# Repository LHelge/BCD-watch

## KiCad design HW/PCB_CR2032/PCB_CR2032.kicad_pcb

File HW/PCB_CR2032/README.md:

# PCB_CR2032
Design of watch PCB to be used with a CR2032 coin cell battery

## Schematic
TODO: add this as images here

## BoM

Reference | Value | Make | Mouser part# | Part | Qty
--------- | ----- | ---- | ---- | ------ | ---
BT1 | CR2032 | Linx | 712-BAT-HLD-001 | BAT-HLD-001 | 1
C1, C2 | 20pF | Yageo | 603-CC805JRNPO9BN200 | CC0805JRNPO9BN200 | 2
C4-C9, C14, C15 | 100nF | Yageo | 603-CC805KRX7R9BB104 | CC0805KRX7R9BB104 | 8
C12 | 11mF | SII | 628-CPH3225A-2K | CPH3225A | 1
C3, C11, C13 | 10uF | Yageo | 603-CC805KKX7R6BB106 | CC0805KKX7R6BB106 | 3
D1-D3 | BAR43CFILM | ST | 511-BAR43CFILM | BAR43CFILM | 3
H00-H03,<br> H10-H13,<br> M00-M03,<br> M10-M13,<br> S00-S03,<br> S10-S13 | LED | Kingbright | 604-APTR3216SECKJ3 | APTR3216SECK/J3-PRV | 24
J1 | STDC14 | Amphenol  | 649-221121-00014T4LF | 20021121-00014T4LF | 1
R1-R20, R23-R26 | 1k | Yageo | 603-RC0805FR-071KL | RC0805FR-071KL | 24
R27-R31 | 10k | Yageo | 603-RC0805FR-0710KL | RC0805FR-0710KL | 5
SW1 | WAKE | Wurth | 710-434331045822 | 434331045822 | 1
U1 | STM32L071CBTx | ST | 511-STM32L071CBT6TR | STM32L071CBT6 | 1
U3 | LIS2DW12 | ST | 511-LIS2DW12TR | LIS2DW12TR | 1
Y1 | 32768 Hz | Epson Timing | 732-FC135-32.76KAA3 | FC-135 32.7680KA-A3 | 1

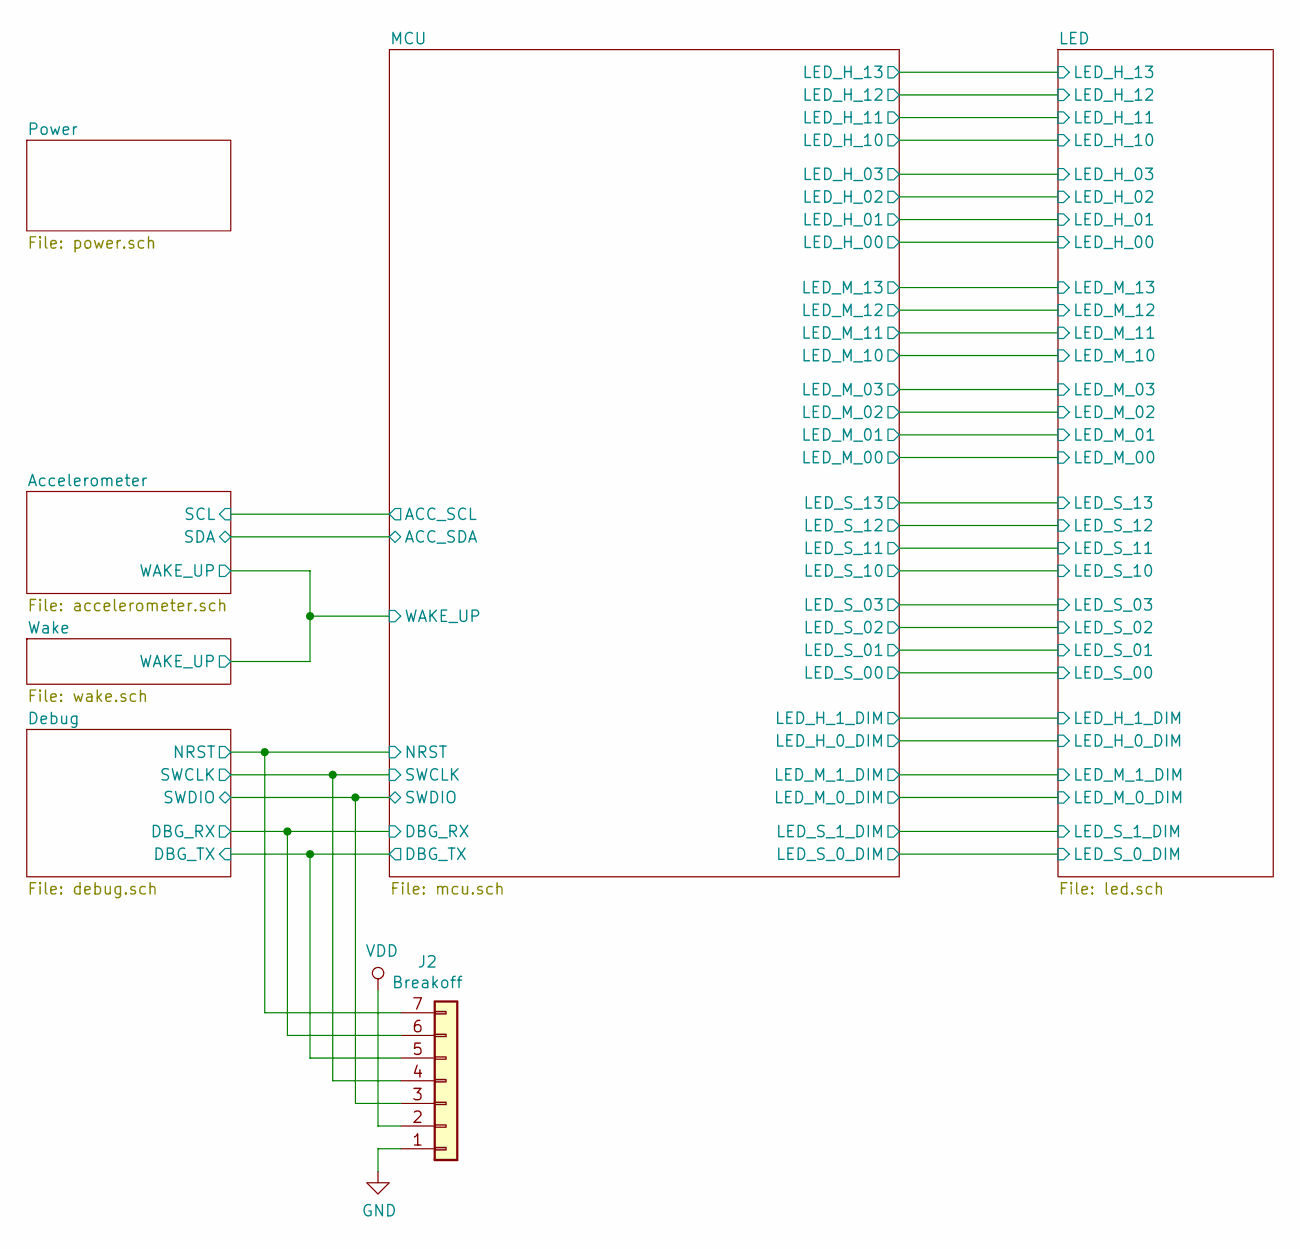
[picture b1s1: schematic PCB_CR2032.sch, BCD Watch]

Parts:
J2: Breakoff; PinHeader_1x07_P1.27mm_Vertical

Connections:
/Debug/DBG_RX: J2.6; also elsewhere on the board
/Debug/DBG_TX: J2.5; also elsewhere on the board
/Debug/NRST: J2.7; also elsewhere on the board
/Debug/SWCLK: J2.4; also elsewhere on the board
/Debug/SWDIO: J2.3; also elsewhere on the board
GND: J2.1; also elsewhere on the board
VDD: J2.2; also elsewhere on the board

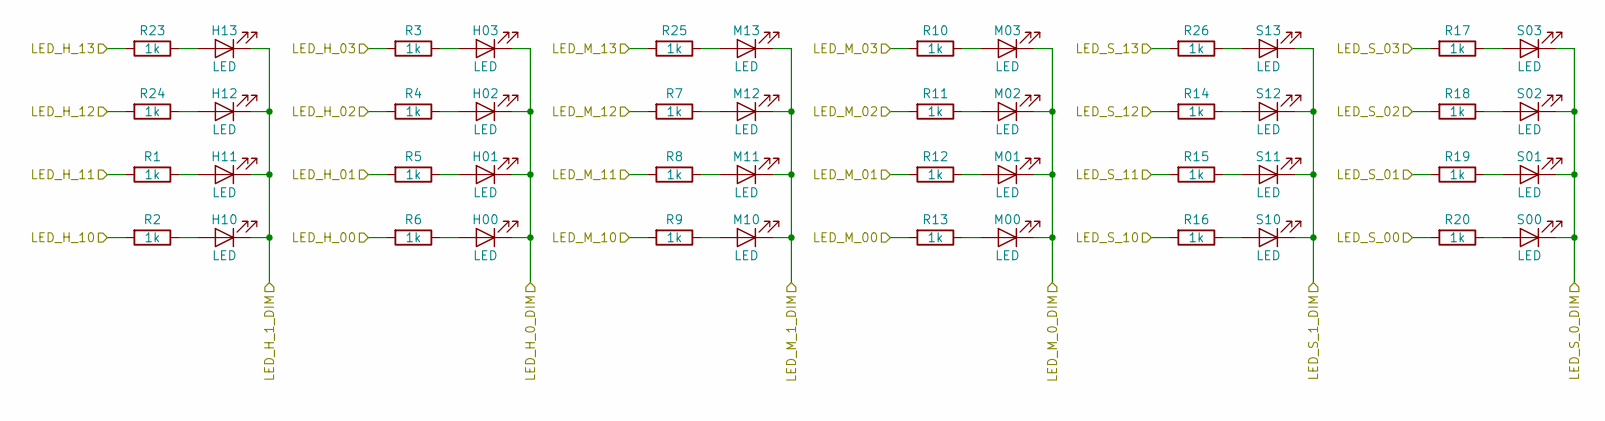
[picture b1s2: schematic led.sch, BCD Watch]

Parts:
H00, H01, H02, H03, H10, H11, H12, H13: LED; LED_1206_3216Metric; Part APTR3216SECK/J3-PRV; Mouser 604-APTR3216SECKJ3
M00, M01, M02, M03, M10, M11, M12, M13: LED; LED_1206_3216Metric; Part APTR3216SECK/J3-PRV; Mouser 604-APTR3216SECKJ3
R1, R2, R3, R4, R5, R6, R7, R8, R9, R10, R11, R12, R13, R14, R15, R16, R17, R18, R19, R20, R23, R24, R25, R26: 1k; R_0603_1608Metric_Pad1.05x0.95mm_HandSolder
S00, S01, S02, S03, S10, S11, S12, S13: LED; LED_1206_3216Metric; Part APTR3216SECK/J3-PRV; Mouser 604-APTR3216SECKJ3

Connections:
/Debug/DBG_RX: R23.2; also elsewhere on the board
/Debug/DBG_TX: R24.2; also elsewhere on the board
/LED/LED_H_00: R6.2; also elsewhere on the board
/LED/LED_H_0_DIM: H00.1 (K), H01.1 (K), H02.1 (K), H03.1 (K); also elsewhere on the board
/LED/LED_H_01: R5.2; also elsewhere on the board
/LED/LED_H_1_DIM: H10.1 (K), H11.1 (K), H12.1 (K), H13.1 (K); also elsewhere on the board
/LED/LED_H_02: R4.2; also elsewhere on the board
/LED/LED_H_03: R3.2; also elsewhere on the board
/LED/LED_H_10: R2.2; also elsewhere on the board
/LED/LED_H_11: R1.2; also elsewhere on the board
/LED/LED_M_00: R13.2; also elsewhere on the board
/LED/LED_M_0_DIM: M00.1 (K), M01.1 (K), M02.1 (K), M03.1 (K); also elsewhere on the board
/LED/LED_M_01: R12.2; also elsewhere on the board
/LED/LED_M_1_DIM: M10.1 (K), M11.1 (K), M12.1 (K), M13.1 (K); also elsewhere on the board
/LED/LED_M_02: R11.2; also elsewhere on the board
/LED/LED_M_03: R10.2; also elsewhere on the board
/LED/LED_M_10: R9.2; also elsewhere on the board
/LED/LED_M_11: R8.2; also elsewhere on the board
/LED/LED_M_12: R7.2; also elsewhere on the board
/LED/LED_M_13: R25.2; also elsewhere on the board
/LED/LED_S_00: R20.2; also elsewhere on the board
/LED/LED_S_0_DIM: S00.1 (K), S01.1 (K), S02.1 (K), S03.1 (K); also elsewhere on the board
/LED/LED_S_01: R19.2; also elsewhere on the board
/LED/LED_S_1_DIM: S10.1 (K), S11.1 (K), S12.1 (K), S13.1 (K); also elsewhere on the board
/LED/LED_S_02: R18.2; also elsewhere on the board
/LED/LED_S_03: R17.2; also elsewhere on the board
/LED/LED_S_10: R16.2; also elsewhere on the board
/LED/LED_S_11: R15.2; also elsewhere on the board
/LED/LED_S_12: R14.2; also elsewhere on the board
/LED/LED_S_13: R26.2; also elsewhere on the board
unnamed: H00.2 (A), R6.1
unnamed: H01.2 (A), R5.1
unnamed: H02.2 (A), R4.1
unnamed: H03.2 (A), R3.1
unnamed: H10.2 (A), R2.1
unnamed: H11.2 (A), R1.1
unnamed: H12.2 (A), R24.1
unnamed: H13.2 (A), R23.1
unnamed: M00.2 (A), R13.1
unnamed: M01.2 (A), R12.1
unnamed: M02.2 (A), R11.1
unnamed: M03.2 (A), R10.1
unnamed: M10.2 (A), R9.1
unnamed: M11.2 (A), R8.1
unnamed: M12.2 (A), R7.1
unnamed: M13.2 (A), R25.1
unnamed: R14.1, S12.2 (A)
unnamed: R15.1, S11.2 (A)
unnamed: R16.1, S10.2 (A)
unnamed: R17.1, S03.2 (A)
unnamed: R18.1, S02.2 (A)
unnamed: R19.1, S01.2 (A)
unnamed: R20.1, S00.2 (A)
unnamed: R26.1, S13.2 (A)

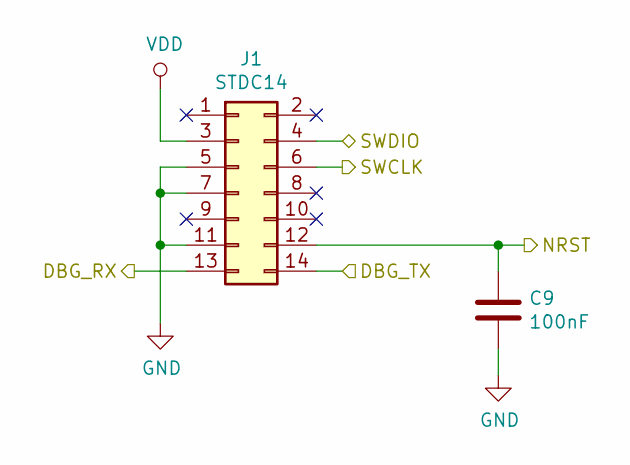
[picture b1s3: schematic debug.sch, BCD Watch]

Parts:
C9: 100nF; C_0603_1608Metric_Pad1.05x0.95mm_HandSolder; jlcpcb CC0603KRX7R9BB104
J1: STDC14; PinHeader_2x07_P1.27mm_Vertical_SMD; Part 20021121-00014T4LF; Mouser 649-221121-00014T4LF

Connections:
/Debug/DBG_RX: J1.13; also elsewhere on the board
/Debug/DBG_TX: J1.14; also elsewhere on the board
/Debug/NRST: C9.1, J1.12; also elsewhere on the board
/Debug/SWCLK: J1.6; also elsewhere on the board
/Debug/SWDIO: J1.4; also elsewhere on the board
GND: C9.2, J1.5, J1.7, J1.11; also elsewhere on the board
VDD: J1.3; also elsewhere on the board

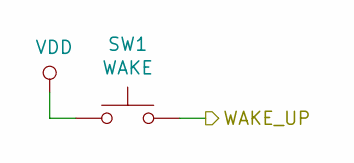
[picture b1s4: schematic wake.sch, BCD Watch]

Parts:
SW1: WAKE; WS-TASU SMT Tact Switch; Part 434331045822; Mouser 710-434331045822

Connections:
/Accelerometer/WAKE_UP: SW1.2; also elsewhere on the board
VDD: SW1.1; also elsewhere on the board

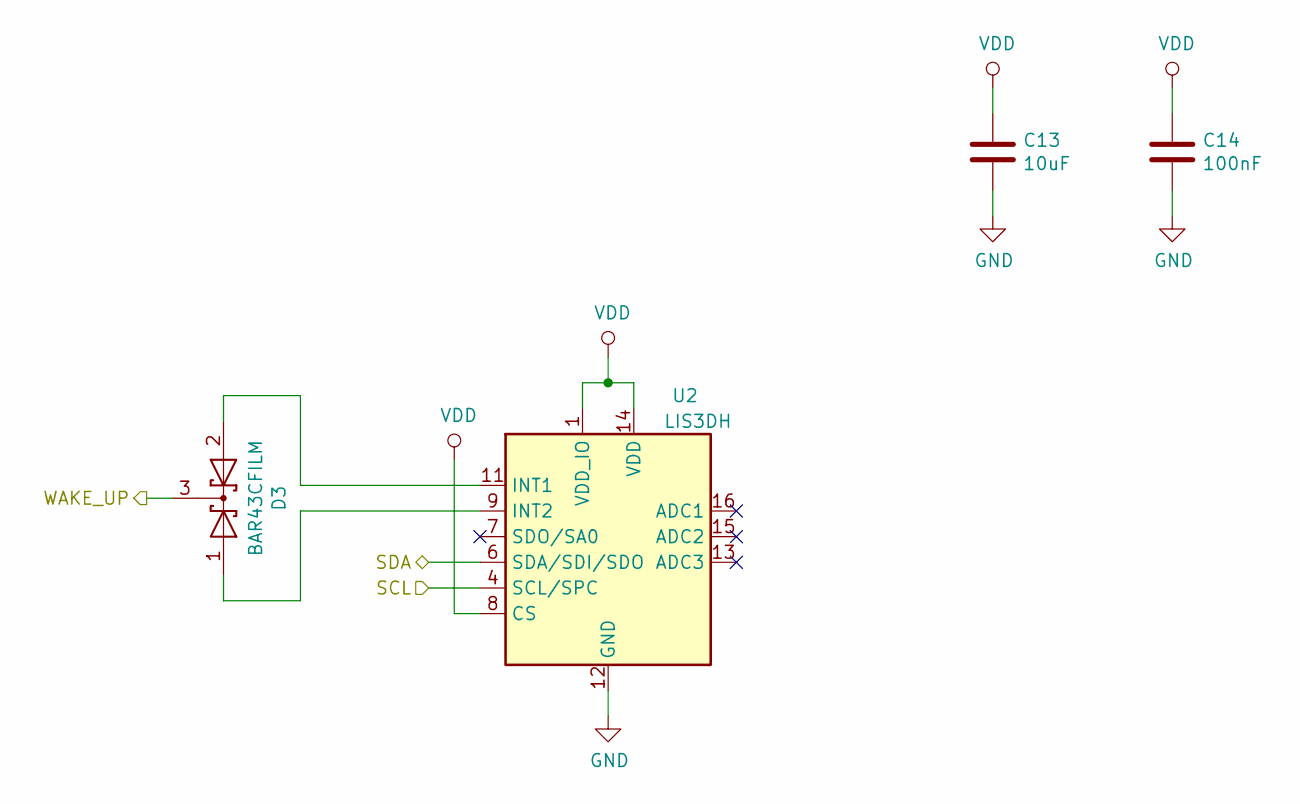
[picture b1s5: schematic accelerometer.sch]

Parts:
C13: 10uF; C_0805_2012Metric_Pad1.15x1.40mm_HandSolder; jlcpcb CL21A106KAYNNNE
C14: 100nF; C_0603_1608Metric_Pad1.05x0.95mm_HandSolder; jlcpcb CC0603KRX7R9BB104
D3: BAR43CFILM; SOT-23_Handsoldering; Part BAR43CFILM; Mouser 511-BAR43CFILM
U2: LIS3DH; LGA-16_3x3mm_P0.5mm_LayoutBorder3x5y; jlcpcb LIS3DHTR

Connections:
/Accelerometer/WAKE_UP: D3.3 (K); also elsewhere on the board
/MCU/ACC_SCL: U2.4 (SCL/SPC); also elsewhere on the board
/MCU/ACC_SDA: U2.6 (SDA/SDI/SDO); also elsewhere on the board
GND: C13.2, C14.2, U2.5 (GND), U2.10 (GND), U2.12 (GND); also elsewhere on the board
unnamed: D3.1 (A), U2.9 (INT2)
unnamed: D3.2 (A), U2.11 (INT1)
VDD: C13.1, C14.1, U2.1 (VDD_IO), U2.8 (CS), U2.14 (VDD); also elsewhere on the board

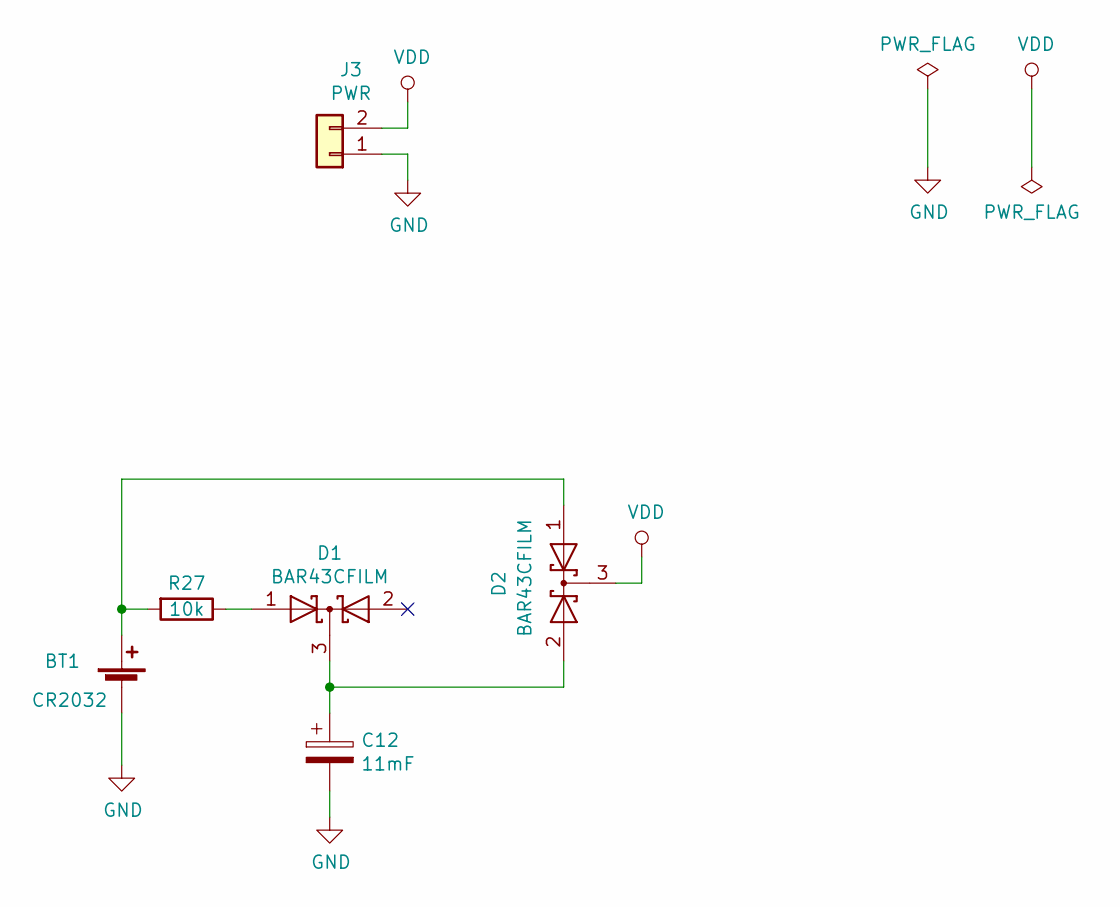
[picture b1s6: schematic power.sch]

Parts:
BT1: CR2032; BAT-HLD-001-xx-OTL; Part BAT-HLD-001; Mouser 712-BAT-HLD-001
C12: 11mF; CPH3225A; Part CPH3225A; Mouser 628-CPH3225A-2K
D1, D2: BAR43CFILM; SOT-23_Handsoldering; Part BAR43CFILM; Mouser 511-BAR43CFILM
J3: PWR; PinHeader_1x02_P1.27mm_Vertical
R27: 10k; R_0603_1608Metric_Pad1.05x0.95mm_HandSolder; LCSC C25804

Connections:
GND: BT1.2 (-), C12.2, J3.1; also elsewhere on the board
unnamed: BT1.1 (+), D2.1 (A), R27.2
unnamed: C12.1, D1.3 (K), D2.2 (A)
unnamed: D1.1 (A), R27.1
VDD: D2.3 (K), J3.2; also elsewhere on the board

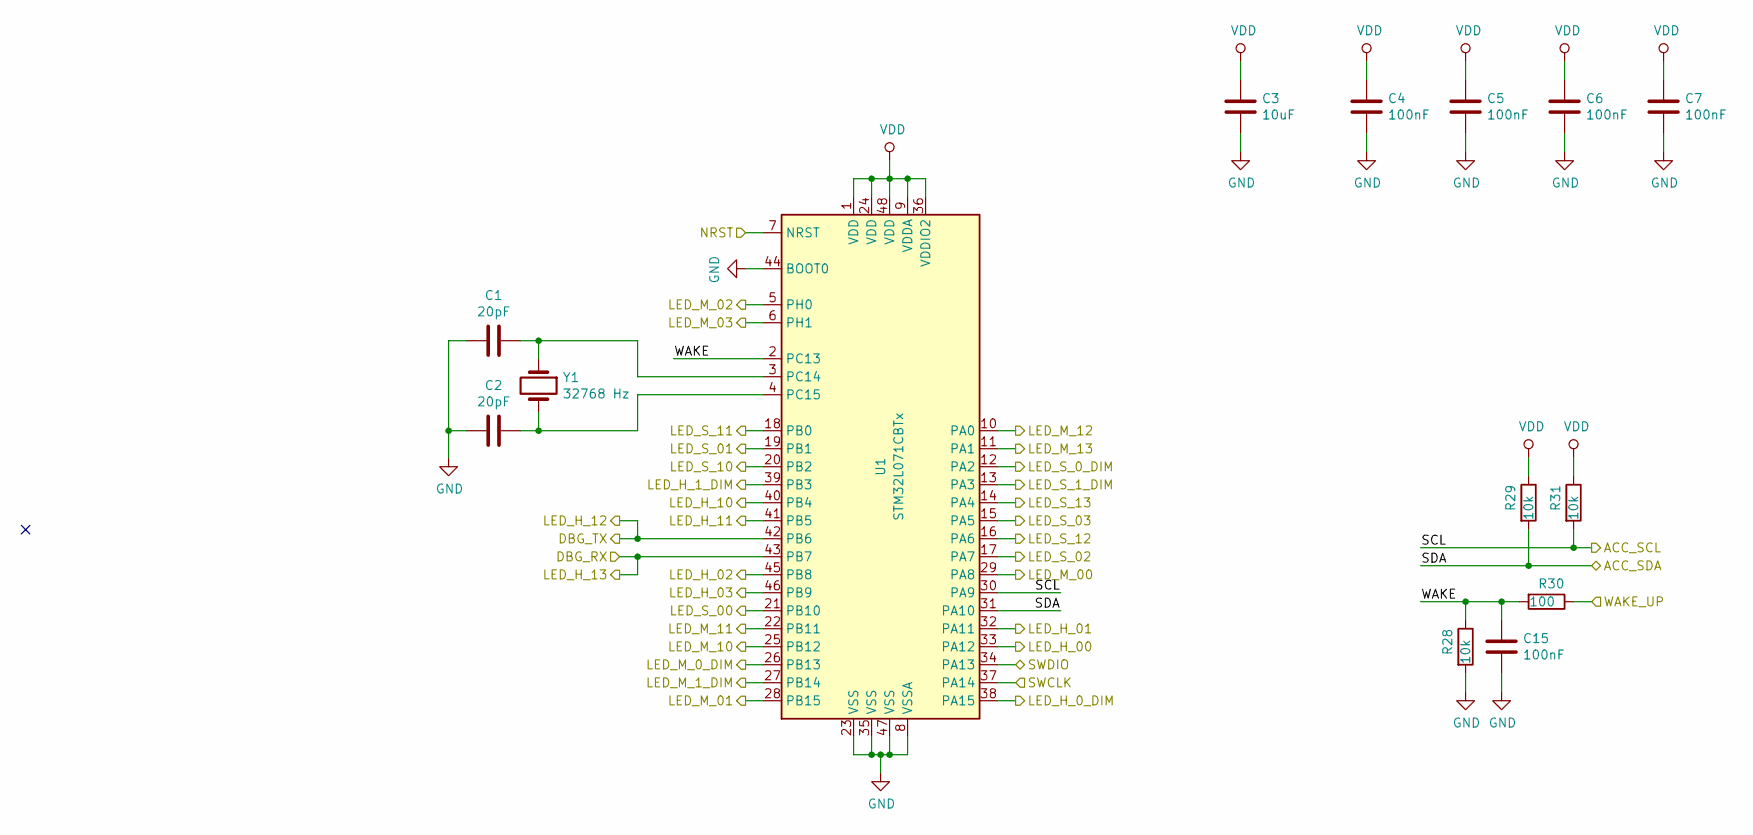
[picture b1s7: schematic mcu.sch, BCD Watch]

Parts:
C1, C2: 20pF; C_0603_1608Metric_Pad1.05x0.95mm_HandSolder; jlcpcb CL10C200JB8NNNC
C3: 10uF; C_0805_2012Metric_Pad1.15x1.40mm_HandSolder; jlcpcb CL21A106KAYNNNE
C4, C5, C6, C7, C15: 100nF; C_0603_1608Metric_Pad1.05x0.95mm_HandSolder; jlcpcb CC0603KRX7R9BB104
R28, R29, R31: 10k; R_0603_1608Metric_Pad1.05x0.95mm_HandSolder; LCSC C25804
R30: 100; R_0603_1608Metric_Pad1.05x0.95mm_HandSolder; LCSC C22775
U1: STM32L071CBTx; LQFP-48_7x7mm_P0.5mm; Part STM32L071CBT6; Mouser 511-STM32L071CBT6TR
Y1: 32768 Hz; FC-135; Part FC-135 32.7680KA-A3; Mouser 732-FC135-32.76KAA3

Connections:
/Accelerometer/WAKE_UP: R30.1; also elsewhere on the board
/Debug/DBG_RX: U1.43 (PB7); also elsewhere on the board
/Debug/DBG_TX: U1.42 (PB6); also elsewhere on the board
/Debug/NRST: U1.7 (NRST); also elsewhere on the board
/Debug/SWCLK: U1.37 (PA14); also elsewhere on the board
/Debug/SWDIO: U1.34 (PA13); also elsewhere on the board
/LED/LED_H_00: U1.33 (PA12); also elsewhere on the board
/LED/LED_H_0_DIM: U1.38 (PA15); also elsewhere on the board
/LED/LED_H_01: U1.32 (PA11); also elsewhere on the board
/LED/LED_H_1_DIM: U1.39 (PB3); also elsewhere on the board
/LED/LED_H_02: U1.45 (PB8); also elsewhere on the board
/LED/LED_H_03: U1.46 (PB9); also elsewhere on the board
/LED/LED_H_10: U1.40 (PB4); also elsewhere on the board
/LED/LED_H_11: U1.41 (PB5); also elsewhere on the board
/LED/LED_M_00: U1.29 (PA8); also elsewhere on the board
/LED/LED_M_0_DIM: U1.26 (PB13); also elsewhere on the board
/LED/LED_M_01: U1.28 (PB15); also elsewhere on the board
/LED/LED_M_1_DIM: U1.27 (PB14); also elsewhere on the board
/LED/LED_M_02: U1.5 (PH0); also elsewhere on the board
/LED/LED_M_03: U1.6 (PH1); also elsewhere on the board
/LED/LED_M_10: U1.25 (PB12); also elsewhere on the board
/LED/LED_M_11: U1.22 (PB11); also elsewhere on the board
/LED/LED_M_12: U1.10 (PA0); also elsewhere on the board
/LED/LED_M_13: U1.11 (PA1); also elsewhere on the board
/LED/LED_S_00: U1.21 (PB10); also elsewhere on the board
/LED/LED_S_0_DIM: U1.12 (PA2); also elsewhere on the board
/LED/LED_S_01: U1.19 (PB1); also elsewhere on the board
/LED/LED_S_1_DIM: U1.13 (PA3); also elsewhere on the board
/LED/LED_S_02: U1.17 (PA7); also elsewhere on the board
/LED/LED_S_03: U1.15 (PA5); also elsewhere on the board
/LED/LED_S_10: U1.20 (PB2); also elsewhere on the board
/LED/LED_S_11: U1.18 (PB0); also elsewhere on the board
/LED/LED_S_12: U1.16 (PA6); also elsewhere on the board
/LED/LED_S_13: U1.14 (PA4); also elsewhere on the board
/MCU/ACC_SCL: R31.2, U1.30 (PA9); also elsewhere on the board
/MCU/ACC_SDA: R29.2, U1.31 (PA10); also elsewhere on the board
/MCU/WAKE: C15.1, R28.1, R30.2, U1.2 (PC13)
GND: C1.2, C2.2, C3.2, C4.2, C5.2, C6.2, C7.2, C15.2, R28.2, U1.8 (VSSA), U1.23 (VSS), U1.35 (VSS), U1.44 (BOOT0), U1.47 (VSS); also elsewhere on the board
unnamed: C1.1, U1.3 (PC14), Y1.1
unnamed: C2.1, U1.4 (PC15), Y1.2
VDD: C3.1, C4.1, C5.1, C6.1, C7.1, R29.1, R31.1, U1.1 (VDD), U1.9 (VDDA), U1.24 (VDD), U1.36 (VDDIO2), U1.48 (VDD); also elsewhere on the board

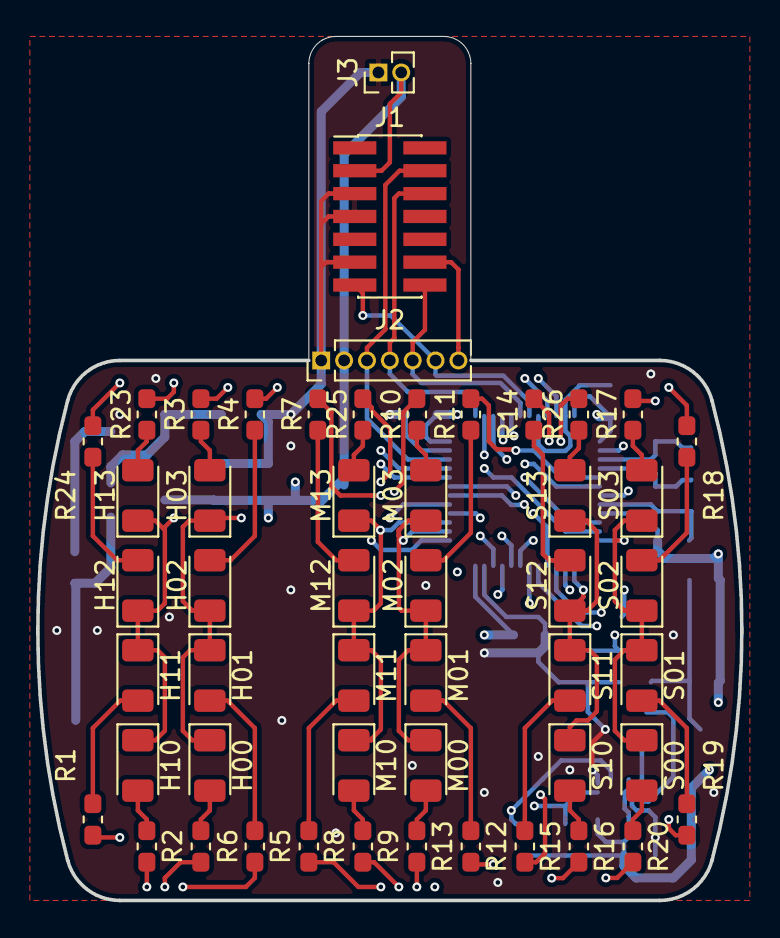
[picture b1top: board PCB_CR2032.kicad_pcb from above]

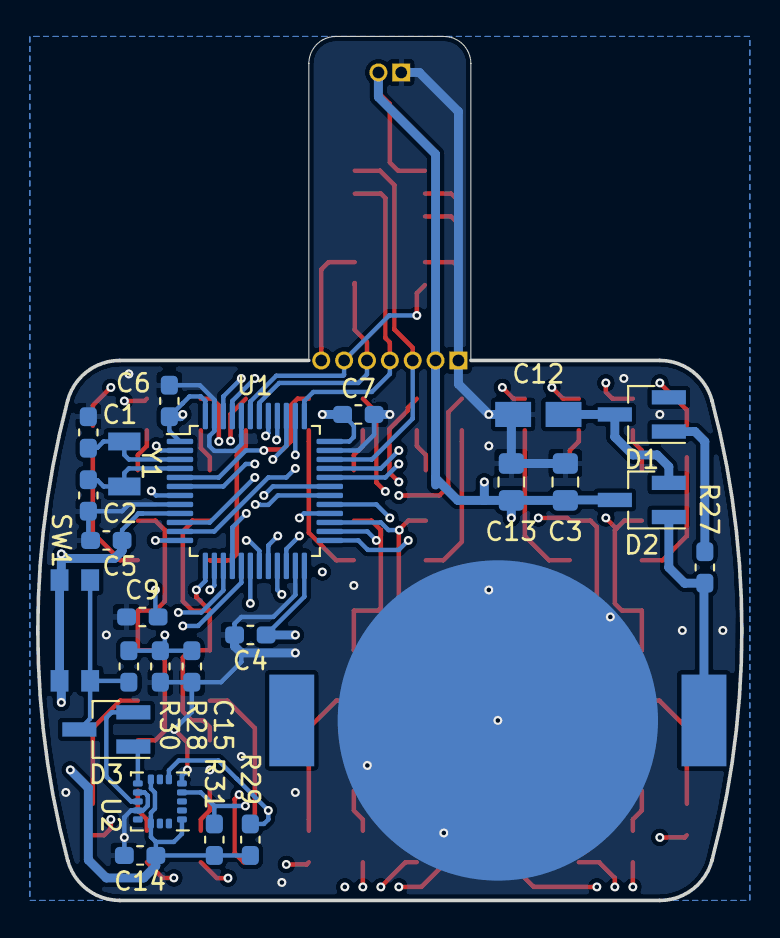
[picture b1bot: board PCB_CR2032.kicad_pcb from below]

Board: 4 copper layers, 39.1 x 47.9 mm, 76 parts (25 on the bottom side), 70 nets.

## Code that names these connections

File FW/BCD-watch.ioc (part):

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Mcu.Name=STM32L071C(B-Z)Tx
Mcu.Package=LQFP48
Mcu.UserName=STM32L071CBTx
PA0.GPIOParameters=GPIO_Label
PA0.GPIO_Label=LED_M_12
PA0.Signal=GPIO_Output
PA1.GPIOParameters=GPIO_Label
PA1.GPIO_Label=LED_M_13
PA1.Signal=GPIO_Output
PA10.GPIOParameters=GPIO_Label
PA10.GPIO_Label=ACC_SDA
PA10.Mode=I2C
PA10.Signal=I2C1_SDA
PA11.GPIOParameters=GPIO_Label
PA11.GPIO_Label=LED_H_01
PA11.Signal=GPIO_Output
PA12.GPIOParameters=GPIO_Label
PA12.GPIO_Label=LED_H_00
PA12.Signal=GPIO_Output
PA13.Mode=Serial_Wire
PA13.Signal=SYS_SWDIO
PA14.Mode=Serial_Wire
PA14.Signal=SYS_SWCLK
PA15.GPIOParameters=GPIO_ModeDefaultPP,GPIO_Label
PA15.GPIO_Label=LED_H_0_DIM
PA15.GPIO_ModeDefaultPP=GPIO_MODE_AF_OD
PA15.Signal=S_TIM2_CH1
PA2.GPIOParameters=GPIO_ModeDefaultPP,GPIO_Label
PA2.GPIO_Label=LED_S_0_DIM
PA2.GPIO_ModeDefaultPP=GPIO_MODE_AF_OD
PA2.Signal=S_TIM2_CH3
PA3.GPIOParameters=GPIO_ModeDefaultPP,GPIO_Label
PA3.GPIO_Label=LED_S_1_DIM
PA3.GPIO_ModeDefaultPP=GPIO_MODE_AF_OD
PA3.Signal=S_TIM2_CH4
PA4.GPIOParameters=GPIO_Label
PA4.GPIO_Label=LED_S_13
PA4.Signal=GPIO_Output
PA5.GPIOParameters=GPIO_Label
PA5.GPIO_Label=LED_S_03
PA5.Signal=GPIO_Output
PA6.GPIOParameters=GPIO_Label
PA6.GPIO_Label=LED_S_12
PA6.Signal=GPIO_Output
PA7.GPIOParameters=GPIO_Label
PA7.GPIO_Label=LED_S_02
PA7.Signal=GPIO_Output
PA8.GPIOParameters=GPIO_Label
PA8.GPIO_Label=LED_M_00
PA8.Signal=GPIO_Output
PA9.GPIOParameters=GPIO_Label
PA9.GPIO_Label=ACC_SCL
PA9.Mode=I2C
PA9.Signal=I2C1_SCL
PB0.GPIOParameters=GPIO_Label
PB0.GPIO_Label=LED_S_11
PB0.Signal=GPIO_Output
PB1.GPIOParameters=GPIO_Label
PB1.GPIO_Label=LED_S_01
PB1.Signal=GPIO_Output
PB10.GPIOParameters=GPIO_Label
PB10.GPIO_Label=LED_S_00
PB10.Signal=GPIO_Output
PB11.GPIOParameters=GPIO_Label
PB11.GPIO_Label=LED_M_11
PB11.Signal=GPIO_Output
PB12.GPIOParameters=GPIO_Label
PB12.GPIO_Label=LED_M_10
PB12.Signal=GPIO_Output
PB13.GPIOParameters=GPIO_Label
PB13.GPIO_Label=LED_M_0_DIM
PB13.Signal=S_TIM21_CH1
PB14.GPIOParameters=GPIO_Label
PB14.GPIO_Label=LED_M_1_DIM
PB14.Signal=S_TIM21_CH2
PB15.GPIOParameters=GPIO_Label
PB15.GPIO_Label=LED_M_01
PB15.Signal=GPIO_Output
PB2.GPIOParameters=GPIO_Label
PB2.GPIO_Label=LED_S_10
PB2.Signal=GPIO_Output
PB3.GPIOParameters=GPIO_ModeDefaultPP,GPIO_Label
PB3.GPIO_Label=LED_H_1_DIM
PB3.GPIO_ModeDefaultPP=GPIO_MODE_AF_OD
PB3.Signal=S_TIM2_CH2
PB4.GPIOParameters=GPIO_Label
PB4.GPIO_Label=LED_H_10
PB4.Signal=GPIO_Output
PB5.GPIOParameters=GPIO_Label
PB5.GPIO_Label=LED_H_11
PB5.Signal=GPIO_Output
PB6.GPIOParameters=GPIO_Label
PB6.GPIO_Label=DBG_TX
PB6.Mode=Asynchronous
PB6.Signal=USART1_TX
PB7.GPIOParameters=GPIO_Label
PB7.GPIO_Label=DBG_RX
PB7.Mode=Asynchronous
PB7.Signal=USART1_RX
PB8.GPIOParameters=GPIO_Label
PB8.GPIO_Label=LED_H_02
PB8.Signal=GPIO_Output
PB9.GPIOParameters=GPIO_Label
PB9.GPIO_Label=LED_H_03
PB9.Signal=GPIO_Output
PC13.GPIOParameters=GPIO_Label
PC13.GPIO_Label=WAKEUP
PC13.Mode=SYS_WakeUp1
PC13.Signal=SYS_WKUP2
PC14-OSC32_IN.Mode=LSE-External-Oscillator
PC14-OSC32_IN.Signal=RCC_OSC32_IN
PC15-OSC32_OUT.Mode=LSE-External-Oscillator
PC15-OSC32_OUT.Signal=RCC_OSC32_OUT
PH0-OSC_IN.GPIOParameters=GPIO_Label
PH0-OSC_IN.GPIO_Label=LED_M_02
PH0-OSC_IN.Signal=GPIO_Output
PH1-OSC_OUT.GPIOParameters=GPIO_Label
PH1-OSC_OUT.GPIO_Label=LED_M_03
PH1-OSC_OUT.Signal=GPIO_Output
RCC.HSE_VALUE=8000000
RCC.SYSCLKFreq_VALUE=32000000
RCC.SYSCLKSource=RCC_SYSCLKSOURCE_PLLCLK
board=custom

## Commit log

2019-11-07 Initial commit of hardware. Rev 0.2 of coin cell PCB
2019-11-07 Initial commit of firmware. Blank generated STM32CubeMX makefile project with pin configuration set according to schematic rev v 0.2
2019-11-08 Added reference manual for MCU and datasheet for good LED candidate
2019-11-08 * Updated Schematic with 1206 leds and 1k 0805 current limiting resistors
    * Restored STDC14 and debug UART, now shared with top led of minute and second. Some other LED pins remapped
    * Updated STM32CubeMX project to reflect schematic changes and generated code again
2019-11-08 * Corrected LED references in schematic
    * Corrected value of oscillator load capacitors
    * Added HW readme with BoM
2019-11-10 Created layout for CR2032 version 1.0, for first prototype order, resulted in a lot of changes in the pin-mapping to make routing easier.
2019-11-11 Added 3D-printable watch for rev 1.0 boards
2019-11-12 Added license file with MIT License
2019-11-12 Compilable generated STM32CubeMX project
2019-11-12 Added CPP support to CubeMX makefile and a template class
2019-11-13 Worked on Rev 2.0 HW with smaller size.
2019-11-14 Worked some more on rev 2.0 schematic. Almost done! Also added 3D-model of battery holder to library.
2019-11-18 updated Rev_2.0 3d-priont files after first print with some small modifications.
2019-11-20 Connected BOOT0 pin to GND after forst board bring up.
2019-11-20 Tested leds and button during board bring-up
2019-11-21 Tested PWM functions successfully
2019-11-21 Added code for UART, not working yet, probably something with clock/baudrate.
2019-11-22 Got the debug serial port to work. Rookie mistake... :D
2019-11-24 Got Accelerometer to work as well.
2019-11-24 Added some time functions. Still not conencted to HW RTC.
2019-11-26 Changed to HSI with PLL @ 32 MHz, added some display code.
2019-11-27 Forgot to set clock config to 32 MHz
2019-11-27 Added button press and accelerometer interrupt wakeup.
2019-12-14 RTC works as well.
2019-12-15 Ordered V2.0 PCB
2019-12-26 Refactored most parts of the firmware
2019-12-26 Added .gitignore for build directory
2019-12-27 Bugfix to statemachine and a way to see if system was resumed from standby
2020-01-01 Solved some bugs wiht accelerometer and RTC, basic functionality to set and display time all there.
2020-01-14 Fix includes for case sensitive file systems
2020-01-15 Updated some 3d-print models
2020-01-15 Added acceleration vector to debug print
2020-01-15 Add generic ReadReg implementations
    Add template versions for ReadReg for various types of data supporting
    bitwise or.
2020-01-15 Added FreeRTOS with a C++ wrapper for tasks
2020-01-15 Tested helper functions for reading multiple byte values from I2C
2020-01-16 Resolved bug i Task constructor.
2020-01-16 Cleaned up Task class and addod some comments
2020-01-16 Wrapped FreeRTOS queues as well.
    Replaced StateMAchine with a separate Task and the internal event queue with a FreeRTOS queue.
2020-01-17 More FreeRTOS additions: * Timers * StreamBuffers (Not tested) * MessageBuffers (Not tested)
    Some changes to the app as well.
    TODO: Put accelerometer driver in a task.
2020-01-20 Changes after comments
2020-01-20 Fix for case sensitive FS
2020-01-20 Use enum for debug-param
    Use enum rather than bool for debug param for increased readability, and
    also moving an ifdef to the Debug class so that it won't have to be
    sprinkled across the code.
2020-01-30 Made Accelerometer run in a thread and added tilt events
2020-02-01 Small changes to PR
2020-02-01 forgot some small things...
2020-02-05 New take on button-events
    Press then release less than press-timeout: button press.
    Press then release longer than press-timeout: long press.
    Button press then press-release longer than press-timeout: button hold.
    Also, while setting time, ticking minutes from 59 to 0 won't tick
    hours. Dim the number you're not currently setting.
    Also fix LED transition flicker.
